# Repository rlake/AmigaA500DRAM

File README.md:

Amiga A500 DRAM

WIP prototype; non-functional and requires debug!

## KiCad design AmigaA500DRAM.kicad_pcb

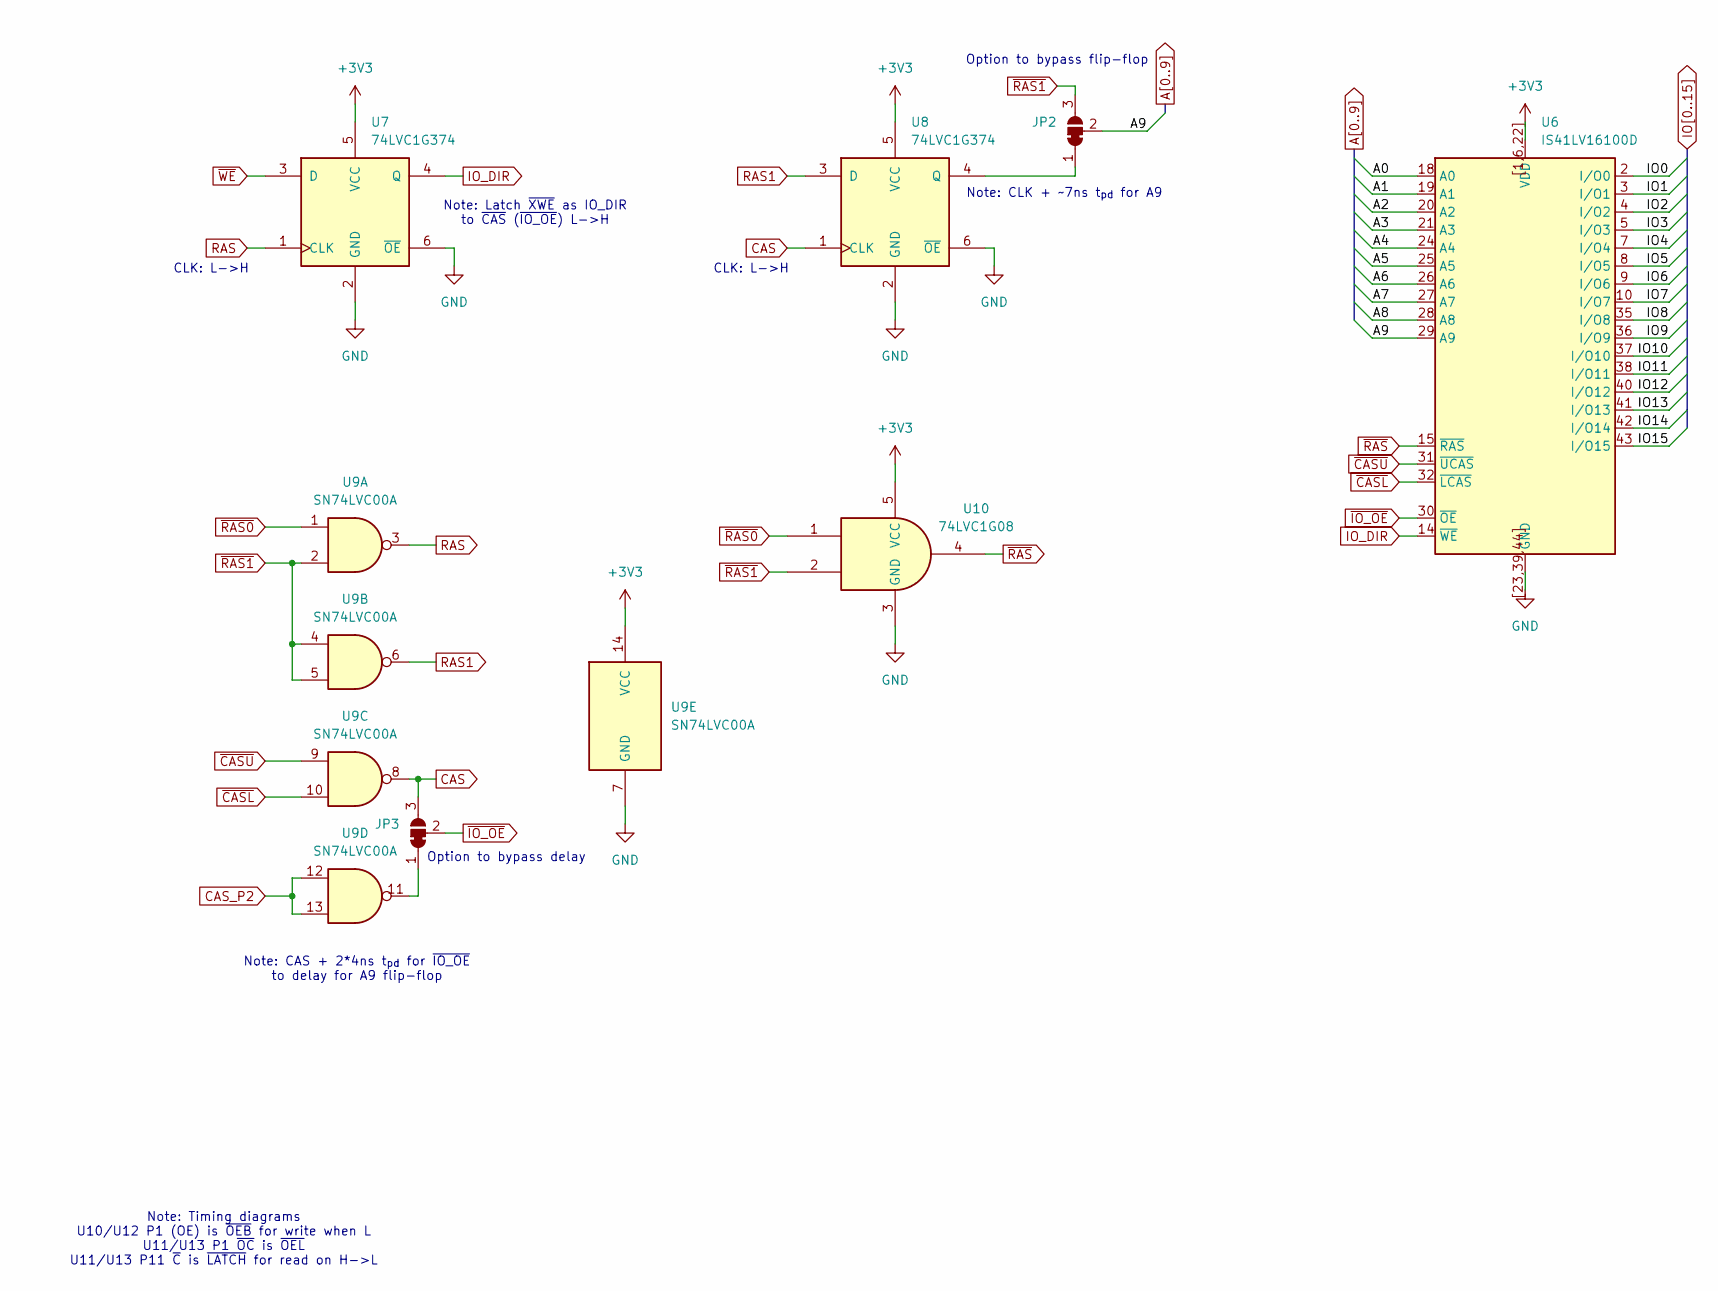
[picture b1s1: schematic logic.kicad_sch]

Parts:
JP2, JP3: SolderJumper_3_Bridged12; SolderJumper-3_P1.3mm_Bridged2Bar12_RoundedPad1.0x1.5mm
U6: IS41LV16100D; TSOP-II-44-50_10.16x20.95mm_P0.8mm
U7, U8: 74LVC1G374; SOT-23-6
U9: SN74LVC00A; TSSOP-14_4.4x5mm_P0.65mm
U10: 74LVC1G08; SOT-23-5

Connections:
+3V3: U6.1 (VDD), U6.6 (VDD), U6.22 (VDD), U6.[1,6,22] (VDD), U7.5 (VCC), U8.5 (VCC), U9.14 (VCC), U10.5 (VCC); also elsewhere on the board
A0: U6.18 (A0); also elsewhere on the board
A1: U6.19 (A1); also elsewhere on the board
A2: U6.20 (A2); also elsewhere on the board
A3: U6.21 (A3); also elsewhere on the board
A4: U6.24 (A4); also elsewhere on the board
A5: U6.25 (A5); also elsewhere on the board
A6: U6.26 (A6); also elsewhere on the board
A7: U6.27 (A7); also elsewhere on the board
A8: U6.28 (A8); also elsewhere on the board
A9: JP2.2 (C), U6.29 (A9)
CAS: JP3.3 (B), U8.1 (CLK), U9.8; also elsewhere on the board
CAS_P2: U9.12, U9.13; also elsewhere on the board
GND: U6.23 (GND), U6.39 (GND), U6.44 (GND), U6.[23,39,44] (GND), U7.2 (GND), U7.6 (~OE), U8.2 (GND), U8.6 (~OE), U9.7 (GND), U10.3 (GND); also elsewhere on the board
IO0: U6.2 (I/O0); also elsewhere on the board
IO1: U6.3 (I/O1); also elsewhere on the board
IO2: U6.4 (I/O2); also elsewhere on the board
IO3: U6.5 (I/O3); also elsewhere on the board
IO4: U6.7 (I/O4); also elsewhere on the board
IO5: U6.8 (I/O5); also elsewhere on the board
IO6: U6.9 (I/O6); also elsewhere on the board
IO7: U6.10 (I/O7); also elsewhere on the board
IO8: U6.35 (I/O8); also elsewhere on the board
IO9: U6.36 (I/O9); also elsewhere on the board
IO10: U6.37 (I/O10); also elsewhere on the board
IO11: U6.38 (I/O11); also elsewhere on the board
IO12: U6.40 (I/O12); also elsewhere on the board
IO13: U6.41 (I/O13); also elsewhere on the board
IO14: U6.42 (I/O14); also elsewhere on the board
IO15: U6.43 (I/O15); also elsewhere on the board
IO_DIR: U6.14 (~WE), U7.4 (Q); also elsewhere on the board
unnamed: JP2.1 (A), U8.4 (Q)
unnamed: JP3.1 (A), U9.11
RAS: U7.1 (CLK), U9.3
RAS1: U8.3 (D), U9.6
~CASL: U6.32 (~LCAS), U9.10; also elsewhere on the board
~CASU: U6.31 (~UCAS), U9.9; also elsewhere on the board
~IO_OE: JP3.2 (C), U6.30 (~OE); also elsewhere on the board
~RAS0: U9.1, U10.1; also elsewhere on the board
~RAS1: JP2.3 (B), U9.2, U9.4, U9.5, U10.2; also elsewhere on the board
~RAS: U6.15 (~RAS), U10.4
~WE: U7.3 (D); also elsewhere on the board

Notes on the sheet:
Note: CAS + 2*4ns t_{pd} for ~{IO_OE} to delay for A9 flip-flop
CLK: L->H
Note: Timing diagrams U10/U12 P1 (OE) is ~{OEB} for write when L U11/U13 P1 ~{OC} is ~{OEL} U11/U13 P11 ~{C} is ~{LATCH} for read on H->L
Note: CLK + ~7ns t_{pd} for A9
Option to bypass flip-flop
Note: Latch ~{XWE} as IO_DIR to ~{CAS} (~{IO_OE}) L->H
Option to bypass delay

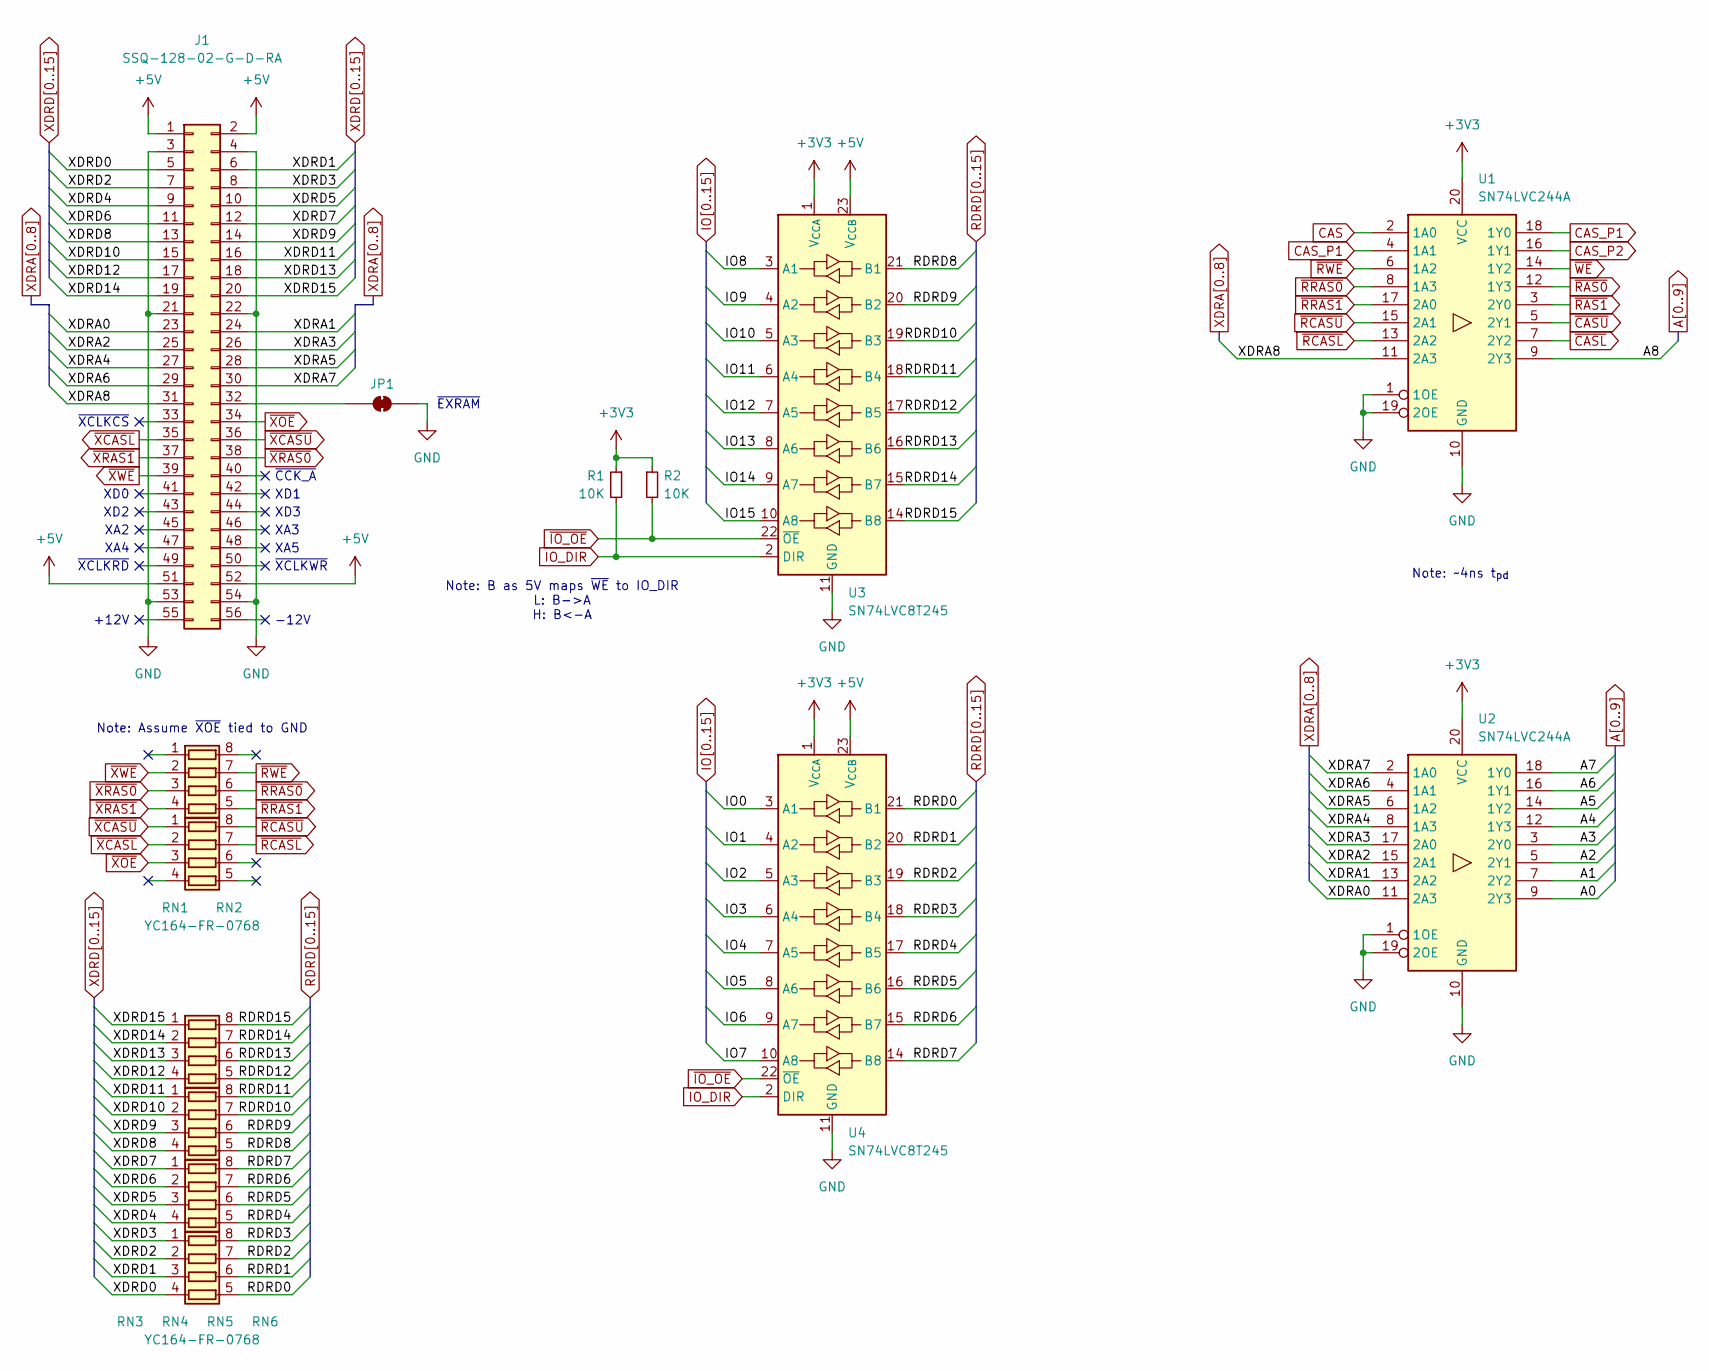
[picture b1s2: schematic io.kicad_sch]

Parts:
J1: SSQ-128-02-G-D-RA; PinSocket_2x28_P2.54mm_Horizontal_A501
JP1: SolderJumper_2_Bridged; SolderJumper-2_P1.3mm_Bridged2Bar_RoundedPad1.0x1.5mm
R1, R2: 10K; R_0805_2012Metric
RN1, RN2, RN3, RN4, RN5, RN6: YC164-FR-0768; R_Array_Convex_4x0603
U1, U2: SN74LVC244A; TSSOP-20_4.4x6.5mm_P0.65mm
U3, U4: SN74LVC8T245; TSSOP-24_4.4x7.8mm_P0.65mm

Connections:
+3V3: R1.1, R2.1, U1.20 (VCC), U2.20 (VCC), U3.1 (V_{CCA}), U4.1 (V_{CCA}); also elsewhere on the board
+5V: J1.1, J1.2, J1.51, J1.52, U3.23 (V_{CCB}), U3.24 (V_{CCB}), U4.23 (V_{CCB}), U4.24 (V_{CCB}); also elsewhere on the board
A0: U2.9 (2Y3); also elsewhere on the board
A1: U2.7 (2Y2); also elsewhere on the board
A2: U2.5 (2Y1); also elsewhere on the board
A3: U2.3 (2Y0); also elsewhere on the board
A4: U2.12 (1Y3); also elsewhere on the board
A5: U2.14 (1Y2); also elsewhere on the board
A6: U2.16 (1Y1); also elsewhere on the board
A7: U2.18 (1Y0); also elsewhere on the board
A8: U1.9 (2Y3); also elsewhere on the board
CAS: U1.2 (1A0); also elsewhere on the board
CAS_P1: U1.4 (1A1), U1.18 (1Y0)
CAS_P2: U1.16 (1Y1); also elsewhere on the board
GND: J1.3, J1.4, J1.21, J1.22, J1.53, J1.54, JP1.2 (B), U1.1 (1OE), U1.10 (GND), U1.19 (2OE), U2.1 (1OE), U2.10 (GND), U2.19 (2OE), U3.11 (GND), U3.12 (GND), U3.13 (GND), U4.11 (GND), U4.12 (GND), U4.13 (GND); also elsewhere on the board
IO0: U4.3 (A1); also elsewhere on the board
IO1: U4.4 (A2); also elsewhere on the board
IO2: U4.5 (A3); also elsewhere on the board
IO3: U4.6 (A4); also elsewhere on the board
IO4: U4.7 (A5); also elsewhere on the board
IO5: U4.8 (A6); also elsewhere on the board
IO6: U4.9 (A7); also elsewhere on the board
IO7: U4.10 (A8); also elsewhere on the board
IO8: U3.3 (A1); also elsewhere on the board
IO9: U3.4 (A2); also elsewhere on the board
IO10: U3.5 (A3); also elsewhere on the board
IO11: U3.6 (A4); also elsewhere on the board
IO12: U3.7 (A5); also elsewhere on the board
IO13: U3.8 (A6); also elsewhere on the board
IO14: U3.9 (A7); also elsewhere on the board
IO15: U3.10 (A8); also elsewhere on the board
IO_DIR: R1.2, U3.2 (DIR), U4.2 (DIR); also elsewhere on the board
unnamed: J1.32, JP1.1 (A)
RDRD0: RN6.5 (R4.2), U4.21 (B1)
RDRD1: RN6.6 (R3.2), U4.20 (B2)
RDRD2: RN6.7 (R2.2), U4.19 (B3)
RDRD3: RN6.8 (R1.2), U4.18 (B4)
RDRD4: RN5.5 (R4.2), U4.17 (B5)
RDRD5: RN5.6 (R3.2), U4.16 (B6)
RDRD6: RN5.7 (R2.2), U4.15 (B7)
RDRD7: RN5.8 (R1.2), U4.14 (B8)
RDRD8: RN4.5 (R4.2), U3.21 (B1)
RDRD9: RN4.6 (R3.2), U3.20 (B2)
RDRD10: RN4.7 (R2.2), U3.19 (B3)
RDRD11: RN4.8 (R1.2), U3.18 (B4)
RDRD12: RN3.5 (R4.2), U3.17 (B5)
RDRD13: RN3.6 (R3.2), U3.16 (B6)
RDRD14: RN3.7 (R2.2), U3.15 (B7)
RDRD15: RN3.8 (R1.2), U3.14 (B8)
XDRA0: J1.23, U2.11 (2A3)
XDRA1: J1.24, U2.13 (2A2)
XDRA2: J1.25, U2.15 (2A1)
XDRA3: J1.26, U2.17 (2A0)
XDRA4: J1.27, U2.8 (1A3)
XDRA5: J1.28, U2.6 (1A2)
XDRA6: J1.29, U2.4 (1A1)
XDRA7: J1.30, U2.2 (1A0)
XDRA8: J1.31, U1.11 (2A3)
XDRD0: J1.5, RN6.4 (R4.1)
XDRD1: J1.6, RN6.3 (R3.1)
XDRD2: J1.7, RN6.2 (R2.1)
XDRD3: J1.8, RN6.1 (R1.1)
XDRD4: J1.9, RN5.4 (R4.1)
XDRD5: J1.10, RN5.3 (R3.1)
XDRD6: J1.11, RN5.2 (R2.1)
XDRD7: J1.12, RN5.1 (R1.1)
XDRD8: J1.13, RN4.4 (R4.1)
XDRD9: J1.14, RN4.3 (R3.1)
XDRD10: J1.15, RN4.2 (R2.1)
XDRD11: J1.16, RN4.1 (R1.1)
XDRD12: J1.17, RN3.4 (R4.1)
XDRD13: J1.18, RN3.3 (R3.1)
XDRD14: J1.19, RN3.2 (R2.1)
XDRD15: J1.20, RN3.1 (R1.1)
~CASL: U1.7 (2Y2); also elsewhere on the board
~CASU: U1.5 (2Y1); also elsewhere on the board
~IO_OE: R2.2, U3.22 (~OE), U4.22 (~OE); also elsewhere on the board
~RAS0: U1.12 (1Y3); also elsewhere on the board
~RAS1: U1.3 (2Y0); also elsewhere on the board
~RCASL: RN2.7 (R2.2), U1.13 (2A2)
~RCASU: RN2.8 (R1.2), U1.15 (2A1)
~RRAS0: RN1.6 (R3.2), U1.8 (1A3)
~RRAS1: RN1.5 (R4.2), U1.17 (2A0)
~RWE: RN1.7 (R2.2), U1.6 (1A2)
~WE: U1.14 (1Y2); also elsewhere on the board
~XCASL: J1.35, RN2.2 (R2.1)
~XCASU: J1.36, RN2.1 (R1.1)
~XOE: J1.34, RN2.3 (R3.1)
~XRAS0: J1.38, RN1.3 (R3.1)
~XRAS1: J1.37, RN1.4 (R4.1)
~XWE: J1.39, RN1.2 (R2.1)

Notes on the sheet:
XA5
Note: ~4ns t_{pd}
~{CCK_A}
XA3
Note: Assume ~{XOE} tied to GND
XD3
XA4
~{XCLKWR}
XD2
XD1
XA2
~{XCLKCS}
~{EXRAM}
+12V
~{XCLKRD}
-12V
XD0
Note: B as 5V maps ~{WE} to IO_DIR L: B->A H: B<-A

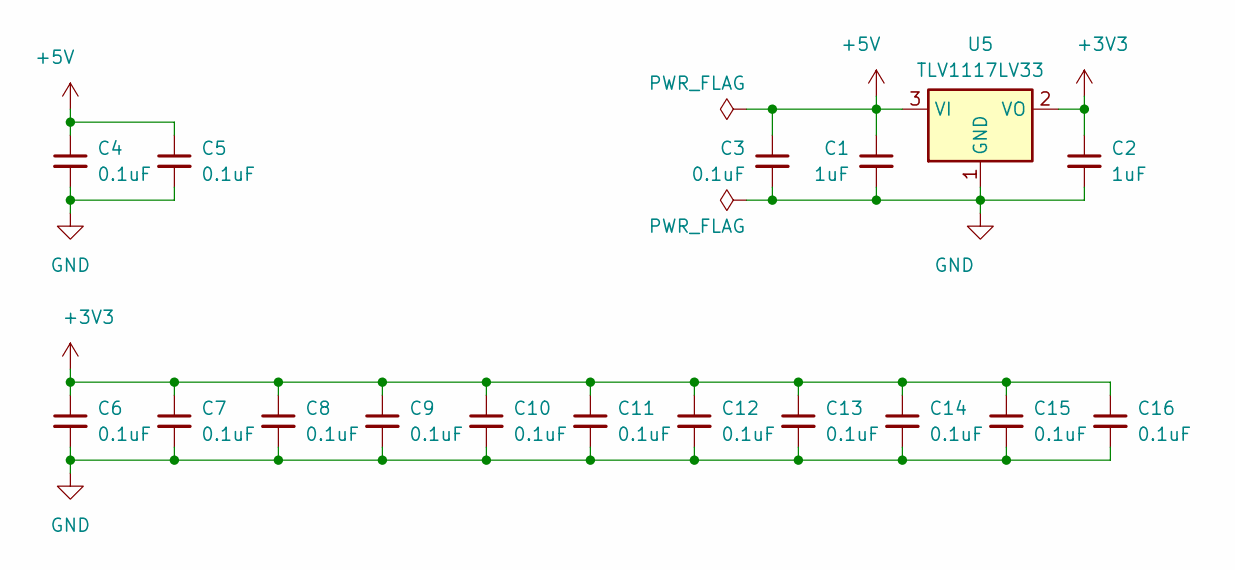
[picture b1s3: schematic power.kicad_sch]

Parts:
C1, C2: 1uF; C_0805_2012Metric
C3, C4, C5, C6, C7, C8, C9, C10, C11, C12, C13, C14, C15, C16: 0.1uF; C_0805_2012Metric
U5: TLV1117LV33; SOT-223-3_TabPin2

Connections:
+3V3: C2.1, C6.1, C7.1, C8.1, C9.1, C10.1, C11.1, C12.1, C13.1, C14.1, C15.1, C16.1, U5.2 (VO); also elsewhere on the board
+5V: C1.1, C3.1, C4.1, C5.1, U5.3 (VI); also elsewhere on the board
GND: C1.2, C2.2, C3.2, C4.2, C5.2, C6.2, C7.2, C8.2, C9.2, C10.2, C11.2, C12.2, C13.2, C14.2, C15.2, C16.2, U5.1 (GND); also elsewhere on the board

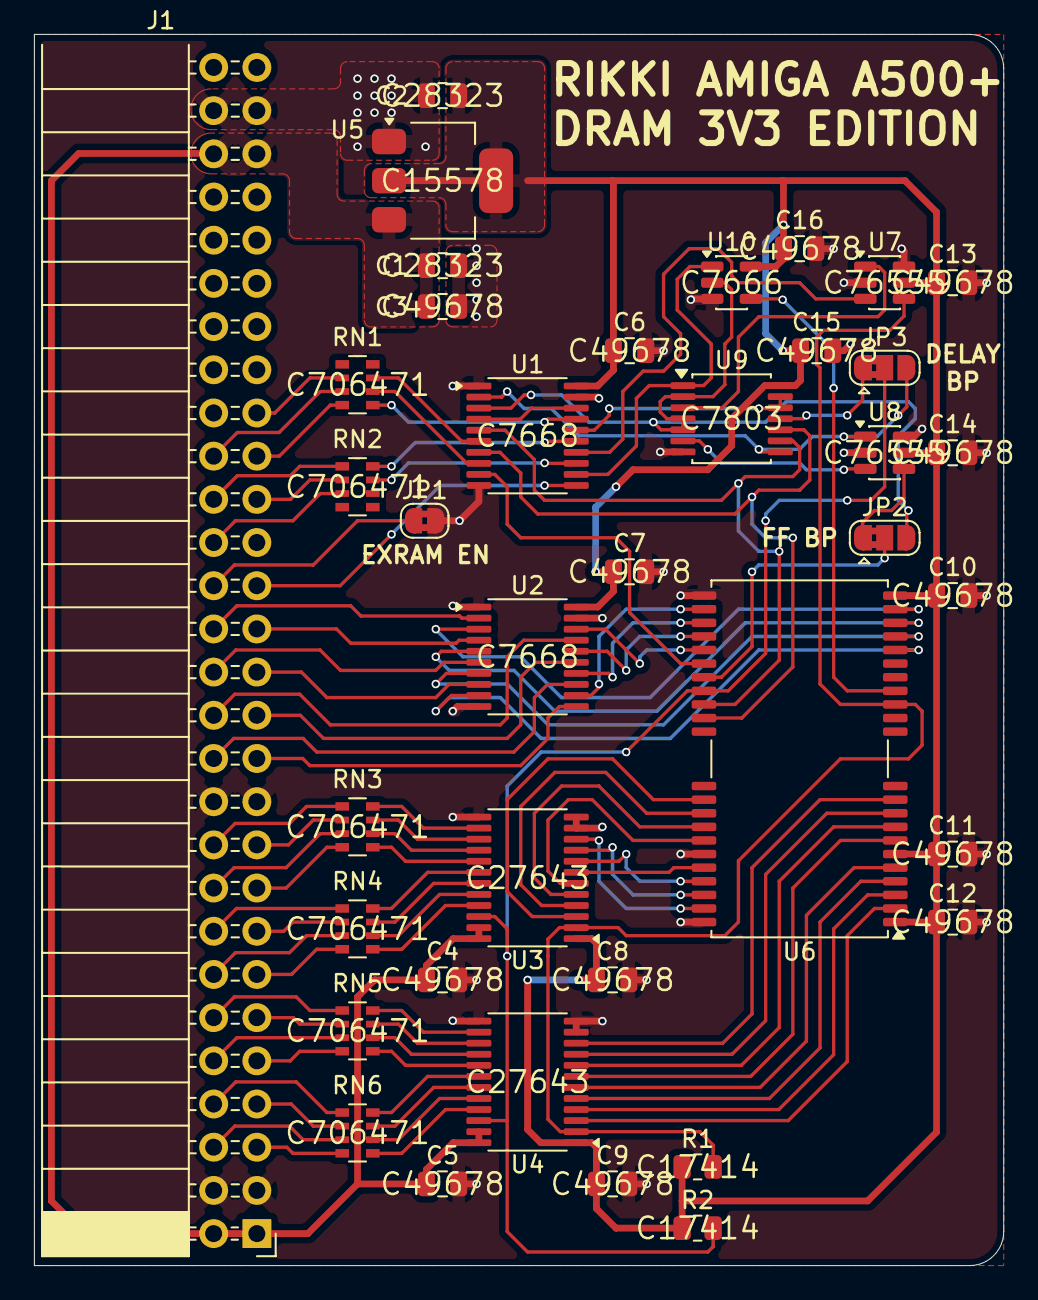
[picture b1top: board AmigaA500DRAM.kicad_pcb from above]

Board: 2 copper layers, 57.0 x 72.4 mm, 38 parts (0 on the bottom side), 97 nets.

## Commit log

2026-04-06 Initial KiCad project
2026-04-06 Add symbols for DRAM, buffer and regulator
2026-04-07 Add footprints for connector, resistor array, DRAM
2026-04-12 Amiga A500 DRAM Schematic
2026-04-12 Amiga A500 DRAM PCB
2026-04-12 Amiga A500 DRAM BOM
2026-04-12 Amiga A500 DRAM PCB Render
2026-04-18 LCSC parts for JLCPCB
2026-05-14 WIP message
